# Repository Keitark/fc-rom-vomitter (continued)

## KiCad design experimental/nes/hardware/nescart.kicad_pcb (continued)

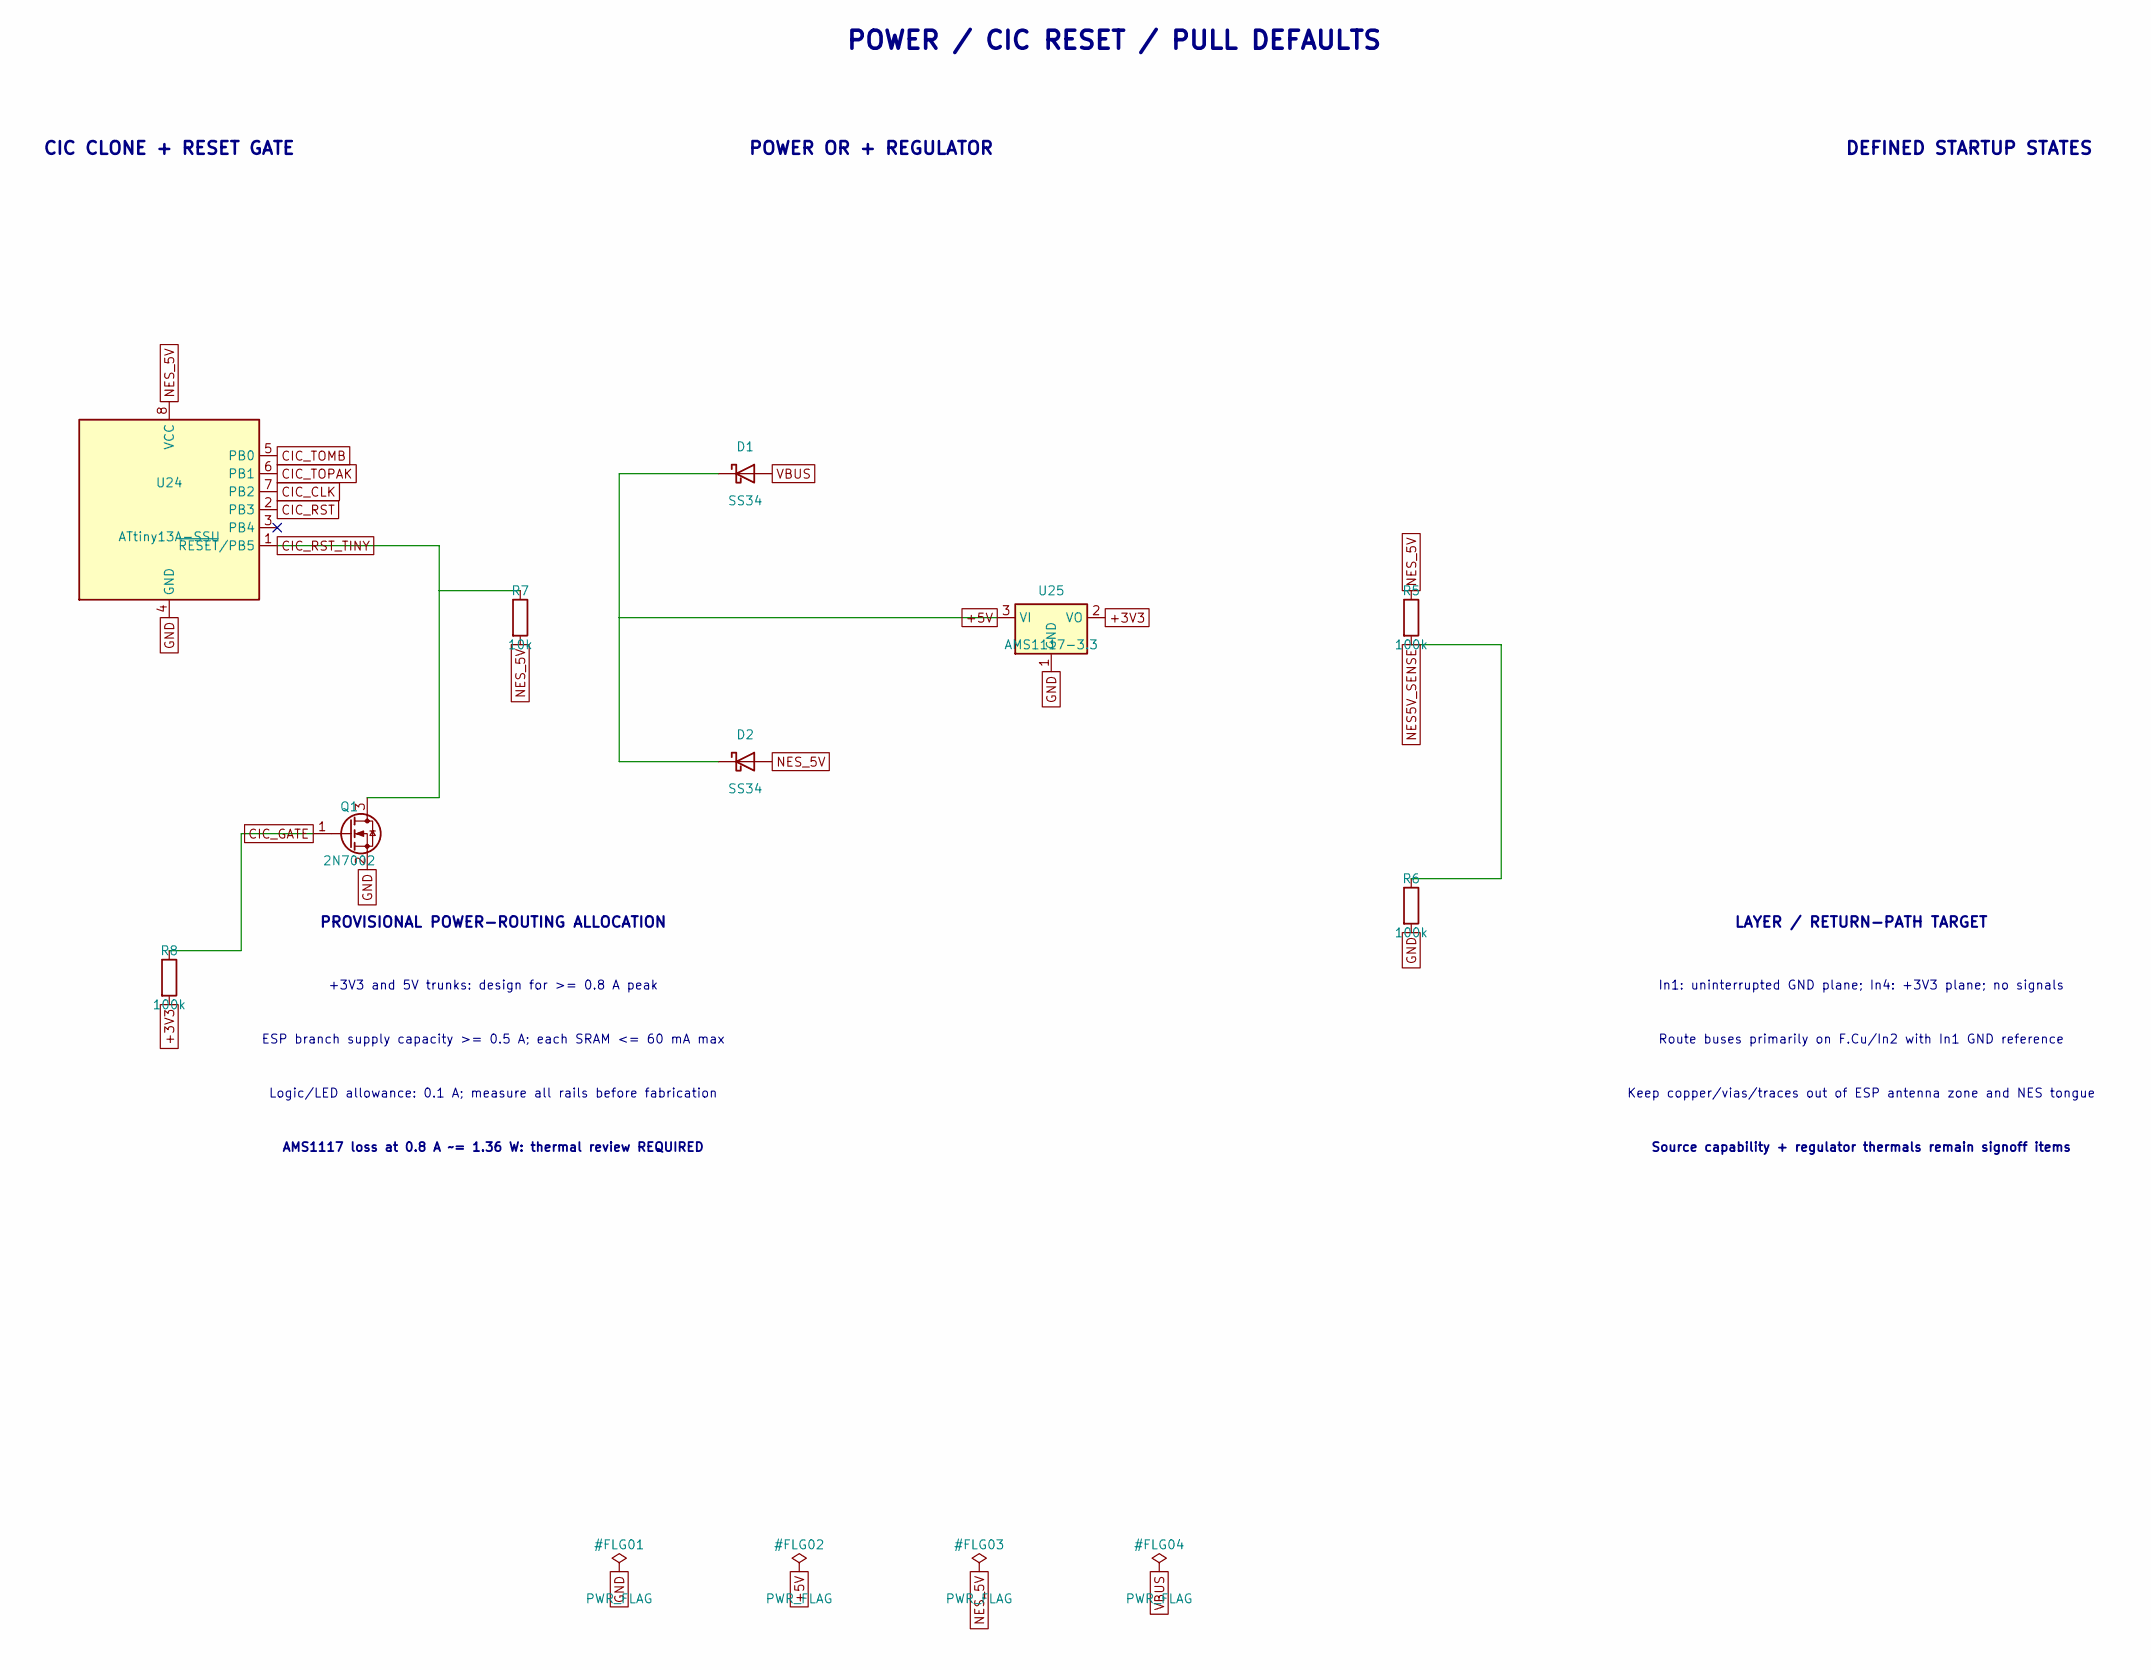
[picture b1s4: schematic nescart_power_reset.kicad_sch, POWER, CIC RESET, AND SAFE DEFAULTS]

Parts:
D1, D2: SS34; D_SMA; MPN SS34
Q1: 2N7002; SOT-23; MPN 2N7002
R5, R6, R8: 100k; R_0603_1608Metric; MPN 0603 100k 1%
R7: 10k; R_0603_1608Metric; MPN 0603 10k 1%
U24: ATtiny13A-SSU; SOIC-8_3.9x4.9mm_P1.27mm; MPN ATTINY13A-SSU
U25: AMS1117-3.3; SOT-223-3_TabPin2; MPN AMS1117-3.3

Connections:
+5V: D1.1 (K), D2.1 (K), U25.3 (VI); also elsewhere on the board
CIC_CLK: U24.7 (PB2); also elsewhere on the board
CIC_GATE: Q1.1 (G), R8.1; also elsewhere on the board
CIC_RST: U24.2 (PB3); also elsewhere on the board
CIC_RST_TINY: Q1.3 (D), R7.1, U24.1 (~RESET/PB5)
CIC_TOMB: U24.5 (PB0); also elsewhere on the board
CIC_TOPAK: U24.6 (PB1); also elsewhere on the board
GND: Q1.2 (S), R6.2, U24.4 (GND), U25.1 (GND); also elsewhere on the board
NES5V_SENSE: R5.2, R6.1; also elsewhere on the board
NES_5V: D2.2 (A), R5.1, R7.2, U24.8 (VCC); also elsewhere on the board
VBUS: D1.2 (A); also elsewhere on the board

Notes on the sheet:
POWER / CIC RESET / PULL DEFAULTS
CIC CLONE + RESET GATE
POWER OR + REGULATOR
DEFINED STARTUP STATES
PROVISIONAL POWER-ROUTING ALLOCATION
+3V3 and 5V trunks: design for >= 0.8 A peak
ESP branch supply capacity >= 0.5 A; each SRAM <= 60 mA max
Logic/LED allowance: 0.1 A; measure all rails before fabrication
AMS1117 loss at 0.8 A ~= 1.36 W: thermal review REQUIRED
LAYER / RETURN-PATH TARGET
In1: uninterrupted GND plane; In4: +3V3 plane; no signals
Route buses primarily on F.Cu/In2 with In1 GND reference
Keep copper/vias/traces out of ESP antenna zone and NES tongue
Source capability + regulator thermals remain signoff items

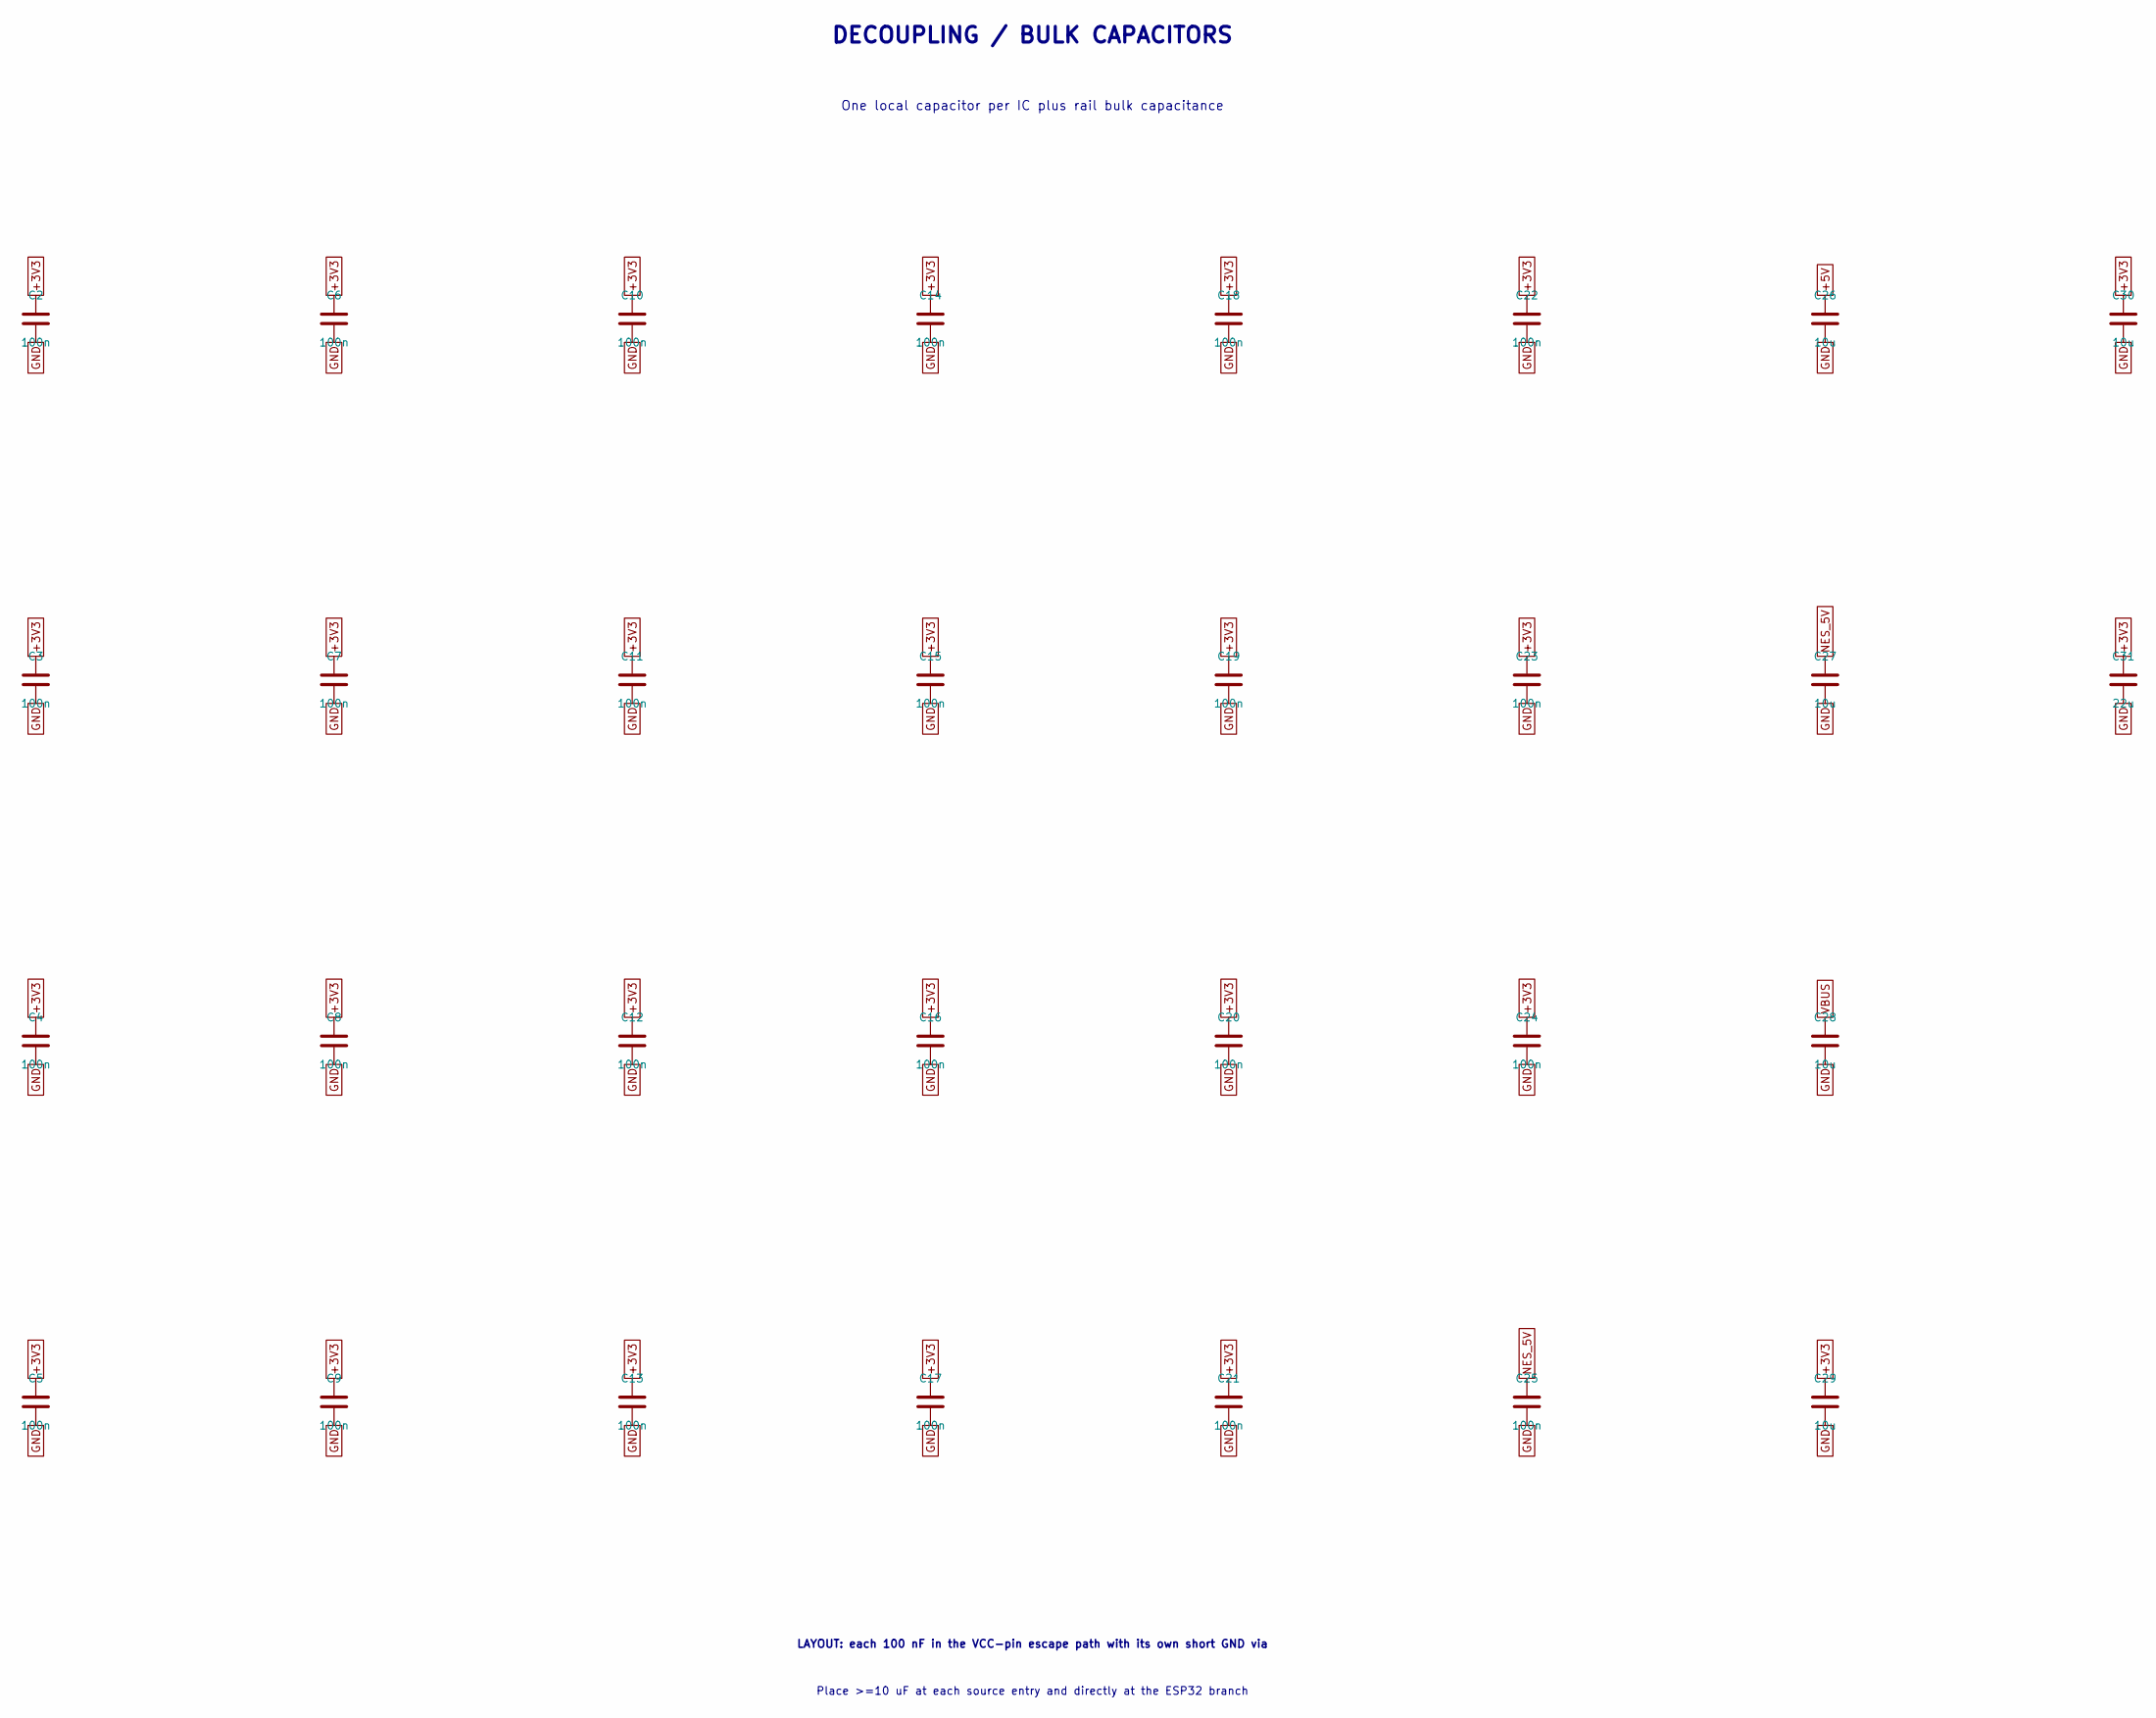
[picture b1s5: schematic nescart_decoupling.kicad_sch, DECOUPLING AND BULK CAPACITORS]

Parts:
C2, C3, C4, C5, C6, C7, C8, C9, C10, C11, C12, C13, C14, C15, C16, C17, C18, C19, C20, C21, C22, C23, C24, C25: 100n; C_0603_1608Metric; MPN 100n X7R
C26, C27, C28, C29, C30: 10u; C_0805_2012Metric; MPN 10u X7R
C31: 22u; C_0805_2012Metric; MPN 22u X7R

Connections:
+5V: C26.1; also elsewhere on the board
GND: C2.2, C3.2, C4.2, C5.2, C6.2, C7.2, C8.2, C9.2, C10.2, C11.2, C12.2, C13.2, C14.2, C15.2, C16.2, C17.2, C18.2, C19.2, C20.2, C21.2, C22.2, C23.2, C24.2, C25.2, C26.2, C27.2, C28.2, C29.2, C30.2, C31.2; also elsewhere on the board
NES_5V: C25.1, C27.1; also elsewhere on the board
VBUS: C28.1; also elsewhere on the board

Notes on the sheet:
DECOUPLING / BULK CAPACITORS
One local capacitor per IC plus rail bulk capacitance
LAYOUT: each 100 nF in the VCC-pin escape path with its own short GND via
Place >=10 uF at each source entry and directly at the ESP32 branch

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
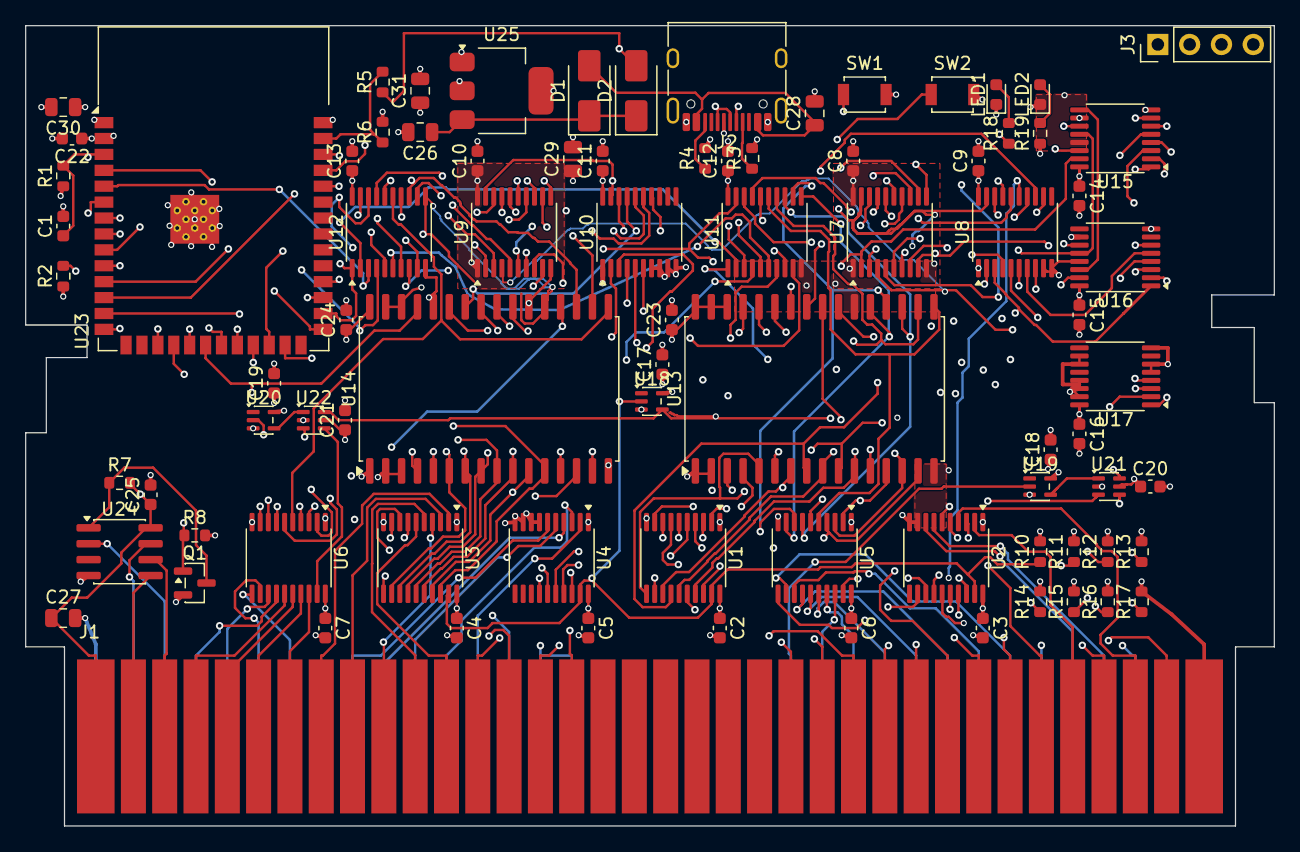
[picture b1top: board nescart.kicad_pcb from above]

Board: 6 copper layers, 99.7 x 63.9 mm, 84 parts (0 on the bottom side), 157 nets.

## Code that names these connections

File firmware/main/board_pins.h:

#pragma once

#include "driver/gpio.h"

/*
 * Released hardware-fc U23 mapping. Keep synchronized with
 * hardware-fc/tools/gen_sch.py ESP32_MAP.
 */
enum {
    PIN_MCU_D0 = GPIO_NUM_4,
    PIN_MCU_D1 = GPIO_NUM_5,
    PIN_MCU_D2 = GPIO_NUM_6,
    PIN_MCU_D3 = GPIO_NUM_7,
    PIN_MCU_D4 = GPIO_NUM_15,
    PIN_MCU_D5 = GPIO_NUM_16,
    PIN_MCU_D6 = GPIO_NUM_17,
    PIN_MCU_D7 = GPIO_NUM_18,

    PIN_SR_SER = GPIO_NUM_8,
    PIN_SR_SRCLK = GPIO_NUM_9,
    PIN_SR_RCLK = GPIO_NUM_10,

    PIN_PRG_WE_N = GPIO_NUM_11,
    PIN_CHR_WE_N = GPIO_NUM_12,
    PIN_PRG_OE_N = GPIO_NUM_13,
    PIN_CHR_OE_N = GPIO_NUM_14,
    PIN_LOAD_MODE = GPIO_NUM_21,
    PIN_PRG_MCU_EN_N = GPIO_NUM_47,
    PIN_CHR_MCU_EN_N = GPIO_NUM_48,
    PIN_MCU_DATA_DIR = GPIO_NUM_35,
    PIN_IO36_SPARE = GPIO_NUM_36,
    PIN_MIRROR_SEL = GPIO_NUM_37,
    PIN_NES5V_SENSE = GPIO_NUM_1,
    PIN_LED_STATUS = GPIO_NUM_2,

    PIN_USB_DN = GPIO_NUM_19,
    PIN_USB_DP = GPIO_NUM_20,
    PIN_DBG_RX = GPIO_NUM_44,
    PIN_DBG_TX = GPIO_NUM_43,
};
